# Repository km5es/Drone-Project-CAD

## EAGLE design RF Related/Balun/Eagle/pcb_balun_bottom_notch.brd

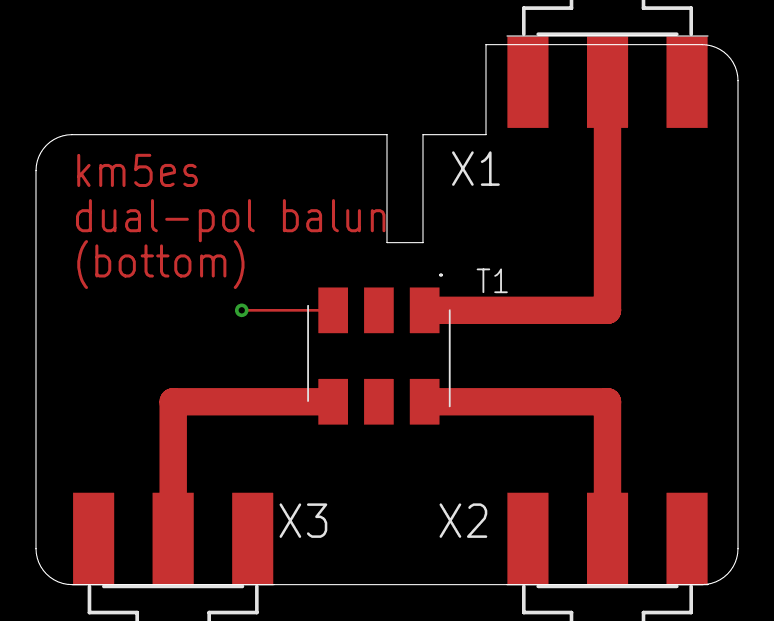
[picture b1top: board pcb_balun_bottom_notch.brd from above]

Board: 2 copper layers, 39.0 x 30.0 mm, 4 parts (0 on the bottom side), 4 nets.

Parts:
T1: ADT1-1WT+; ADT11WT
X1, X2, X3: SMA-142-0701-801/806; J502-ND-142-0701-801/806

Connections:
GND: T1.3, X1.G@1, X1.G@2, X1.G@3, X1.G@4, X2.G@1, X2.G@2, X2.G@3, X2.G@4, X3.G@1, X3.G@2, X3.G@3, X3.G@4
unnamed: T1.1, X1.1
unnamed: T1.6, X2.1
unnamed: T1.4, X3.1

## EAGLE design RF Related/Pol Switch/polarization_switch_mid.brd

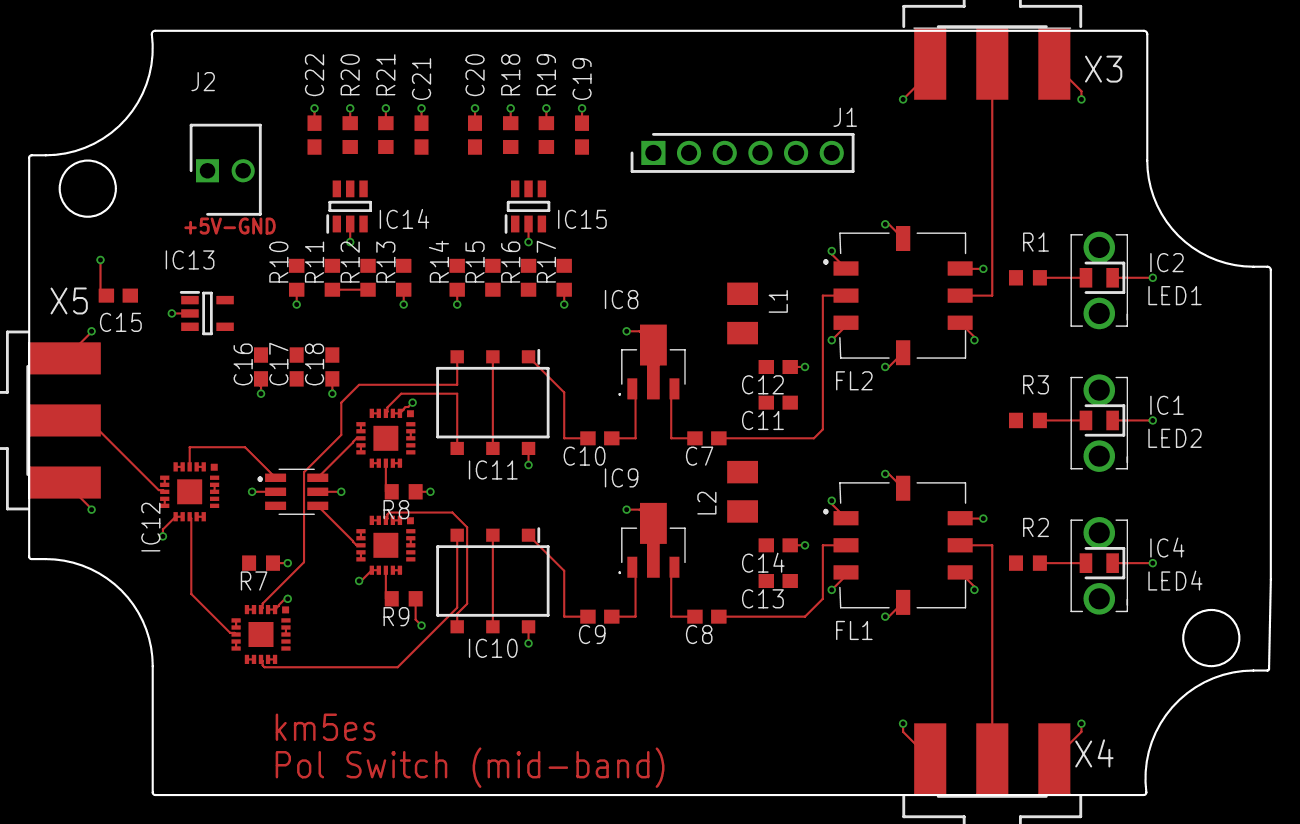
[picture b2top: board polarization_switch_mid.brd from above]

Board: 2 copper layers, 88.4 x 54.4 mm, 61 parts (0 on the bottom side), 40 nets.

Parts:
C7, C8, C9, C10: 2.2e-6; C0603
C11, C13: 10e-6; C0603
C12, C14: 1e-9; C0603
C15: 1e-6; C0603
C16: 0.01e-6; C0603
C17: 3.3e-6; C0603
C18, C19, C20, C21, C22: 100e-12; C0603
FL1, FL2: RBP-135+; RBP135
IC1, IC2, IC4: VLPR-24-858-2; VLPR248582
IC3, IC5, IC6, IC7: HSWA2-30DR+; DG983-1
IC8, IC9: PHA-13LN+; PHA13LN
IC10, IC11: ADP-2-1+_MINICIRCUITS; SOTFL254P691X411-6N
IC12: QCV-151+; QCV151
IC13: MAX8878EUK28+T; SOT95P280X145-5N
IC14, IC15: SN74LVC2G17DBVT; SOT95P280X145-6N
J1: M20-9730645; HDRV6W66P0X254_1X6_1524X254X96
J2: 171856-0002; SHDR2W90P0X254_1X2_493X635X106
L1, L2: 15e-6; L3225M
LED1, LED2, LED4: APT2012LZGCK; LEDC2012X85N
R1, R2, R3: 430; R0603
R7, R8, R9: 50; R0603
R10, R13, R14, R17: 10e6; R0603
R11, R12, R15, R16: 1e6; R0603
R18, R19, R20, R21: 10e3; R0603
X3, X4, X5: SMA-142-0701-801/806; J502-ND-142-0701-801/806

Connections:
GND: C11.1, C12.1, C13.1, C14.1, C15.2, C16.2, C17.2, C18.2, C19.1, C20.2, C21.1, C22.2, FL1.1, FL1.3, FL1.4, FL1.5, FL1.7, FL1.8, FL2.1, FL2.3, FL2.4, FL2.5, FL2.7, FL2.8, IC3.1, IC3.2, IC3.4, IC3.5, IC3.6, IC3.7, IC3.9, IC3.10, IC3.11, IC3.12, IC3.14, IC3.15, IC3.18, IC3.19, IC3.X, IC5.1, IC5.2, IC5.4, IC5.5, IC5.6, IC5.7, IC5.9, IC5.10, IC5.11, IC5.12, IC5.14, IC5.15, IC5.18, IC5.19, IC5.X, IC6.1, IC6.2, IC6.4, IC6.5, IC6.6, IC6.7, IC6.9, IC6.10, IC6.11, IC6.12, IC6.14, IC6.15, IC6.18, IC6.19, IC6.X, IC7.1, IC7.2, IC7.4, IC7.5, IC7.6, IC7.7, IC7.9, IC7.10, IC7.11, IC7.12, IC7.14, IC7.15, IC7.18, IC7.19, IC7.X, IC8.2, IC8.4, IC9.2, IC9.4, IC10.6, IC11.6, IC12.2, IC12.5, IC13.2, IC14.2, IC15.2, J1.5, J1.6, J2.2, LED1.1, LED2.1, LED4.1, R7.1, R8.1, R9.1, R10.1, R13.1, R14.1, R17.1, R18.2, R19.2, R20.2, R21.2, X3.G@1, X3.G@2, X3.G@3, X3.G@4, X4.G@1, X4.G@2, X4.G@3, X4.G@4, X5.G@1, X5.G@2, X5.G@3, X5.G@4
unnamed: LED2.2, R3.2
unnamed: LED1.2, R1.2
unnamed: LED4.2, R2.2
unnamed: IC5.13, IC10.3
unnamed: IC3.8, X5.1
unnamed: C10.2, IC11.1
unnamed: IC7.3, IC10.4
unnamed: C20.1, IC5.17, IC15.6, R18.1
unnamed: IC7.8, IC12.4
unnamed: C10.1, IC8.1
unnamed: IC3.3, IC12.1
unnamed: IC3.13, IC5.8
unnamed: IC6.8, IC12.6
unnamed: IC6.3, IC11.4
unnamed: IC6.13, R8.2
unnamed: C7.2, IC8.3, L1.2
unnamed: C9.2, IC10.1
unnamed: IC11.2, IC11.5
unnamed: IC5.3, IC11.3
unnamed: IC10.2, IC10.5
unnamed: C9.1, IC9.1
unnamed: C8.2, IC9.3, L2.2
unnamed: C7.1, FL2.2
unnamed: FL2.6, X3.1
unnamed: C8.1, FL1.2
unnamed: FL1.6, X4.1
unnamed: IC12.3, R7.2
unnamed: IC7.13, R9.2
unnamed: C11.2, C12.2, C13.2, C14.2, C15.1, IC13.1, IC13.3, J2.1, L1.1, L2.1
unnamed: IC14.1, J1.1, R2.1, R10.2, R11.2
unnamed: C19.2, IC5.16, IC15.4, R19.1
unnamed: C17.1, C18.1, IC3.20, IC5.20, IC6.20, IC7.20, IC13.5, IC14.5, IC15.5, R11.1, R12.1
unnamed: C16.1, IC13.4
unnamed: C22.1, IC3.17, IC6.17, IC7.17, IC14.6, R20.1
unnamed: IC14.3, J1.2, R12.2, R13.2
unnamed: IC15.1, J1.3, R1.1, R14.2, R15.2
unnamed: IC15.3, J1.4, R3.1, R16.2, R17.2
unnamed: C21.2, IC3.16, IC6.16, IC7.16, IC14.4, R21.1
unnamed: R15.1, R16.1

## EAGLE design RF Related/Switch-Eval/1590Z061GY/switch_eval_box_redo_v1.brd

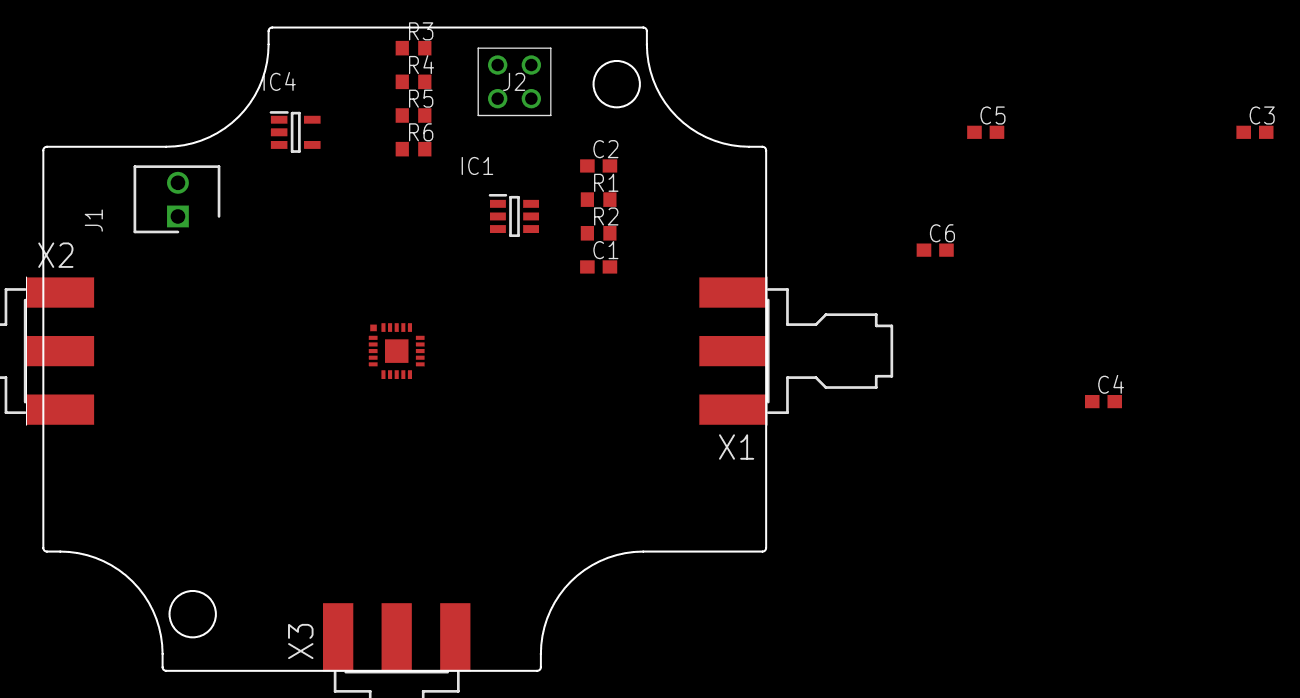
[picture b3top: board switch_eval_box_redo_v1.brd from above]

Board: 2 copper layers, 55.9 x 48.6 mm, 20 parts (0 on the bottom side), 11 nets, no tracks yet.

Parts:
C1, C2, C6: 100e-12; C0603
C3: 1e-6; C0603
C4: 0.01e-6; C0603
C5: 3.3e-6; C0603
IC1: SN74LVC2G17DBVT; SOT95P280X145-6N
IC2: HSWA2-30DR+; DG983-1
IC4: MAX8878EUK28+T; SOT95P280X145-5N
J1: 171856-0002; SHDR2W90P0X254_1X2_493X635X106
J2: M20-7830246; M207830246
R1, R2: 10e3; R0603
R3, R6: 10e6; R0603
R4, R5: 1e6; R0603
X1, X2, X3: SMA-142-0701-801/806; J502-ND-142-0701-801/806

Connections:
GND: C1.1, C2.2, C3.2, C4.2, C5.2, C6.2, IC1.2, IC2.1, IC2.2, IC2.4, IC2.5, IC2.6, IC2.7, IC2.9, IC2.10, IC2.11, IC2.12, IC2.14, IC2.15, IC2.18, IC2.19, IC2.X, IC4.2, J1.2, J2.1, J2.2, R1.2, R2.2, R3.1, R6.1, X1.G@1, X1.G@2, X1.G@3, X1.G@4, X2.G@1, X2.G@2, X2.G@3, X2.G@4, X3.G@1, X3.G@2, X3.G@3, X3.G@4
unnamed: IC1.3, J2.3, R3.2, R4.2
unnamed: C3.1, IC4.1, IC4.3, J1.1
unnamed: C4.1, IC4.4
unnamed: IC1.1, J2.4, R5.2, R6.2
unnamed: C5.1, C6.1, IC1.5, IC2.20, IC4.5, R4.1, R5.1
unnamed: IC2.3, X3.1
unnamed: C2.1, IC1.6, IC2.17, R1.1
unnamed: IC2.13, X1.1
unnamed: C1.2, IC1.4, IC2.16, R2.1
unnamed: IC2.8, X2.1
